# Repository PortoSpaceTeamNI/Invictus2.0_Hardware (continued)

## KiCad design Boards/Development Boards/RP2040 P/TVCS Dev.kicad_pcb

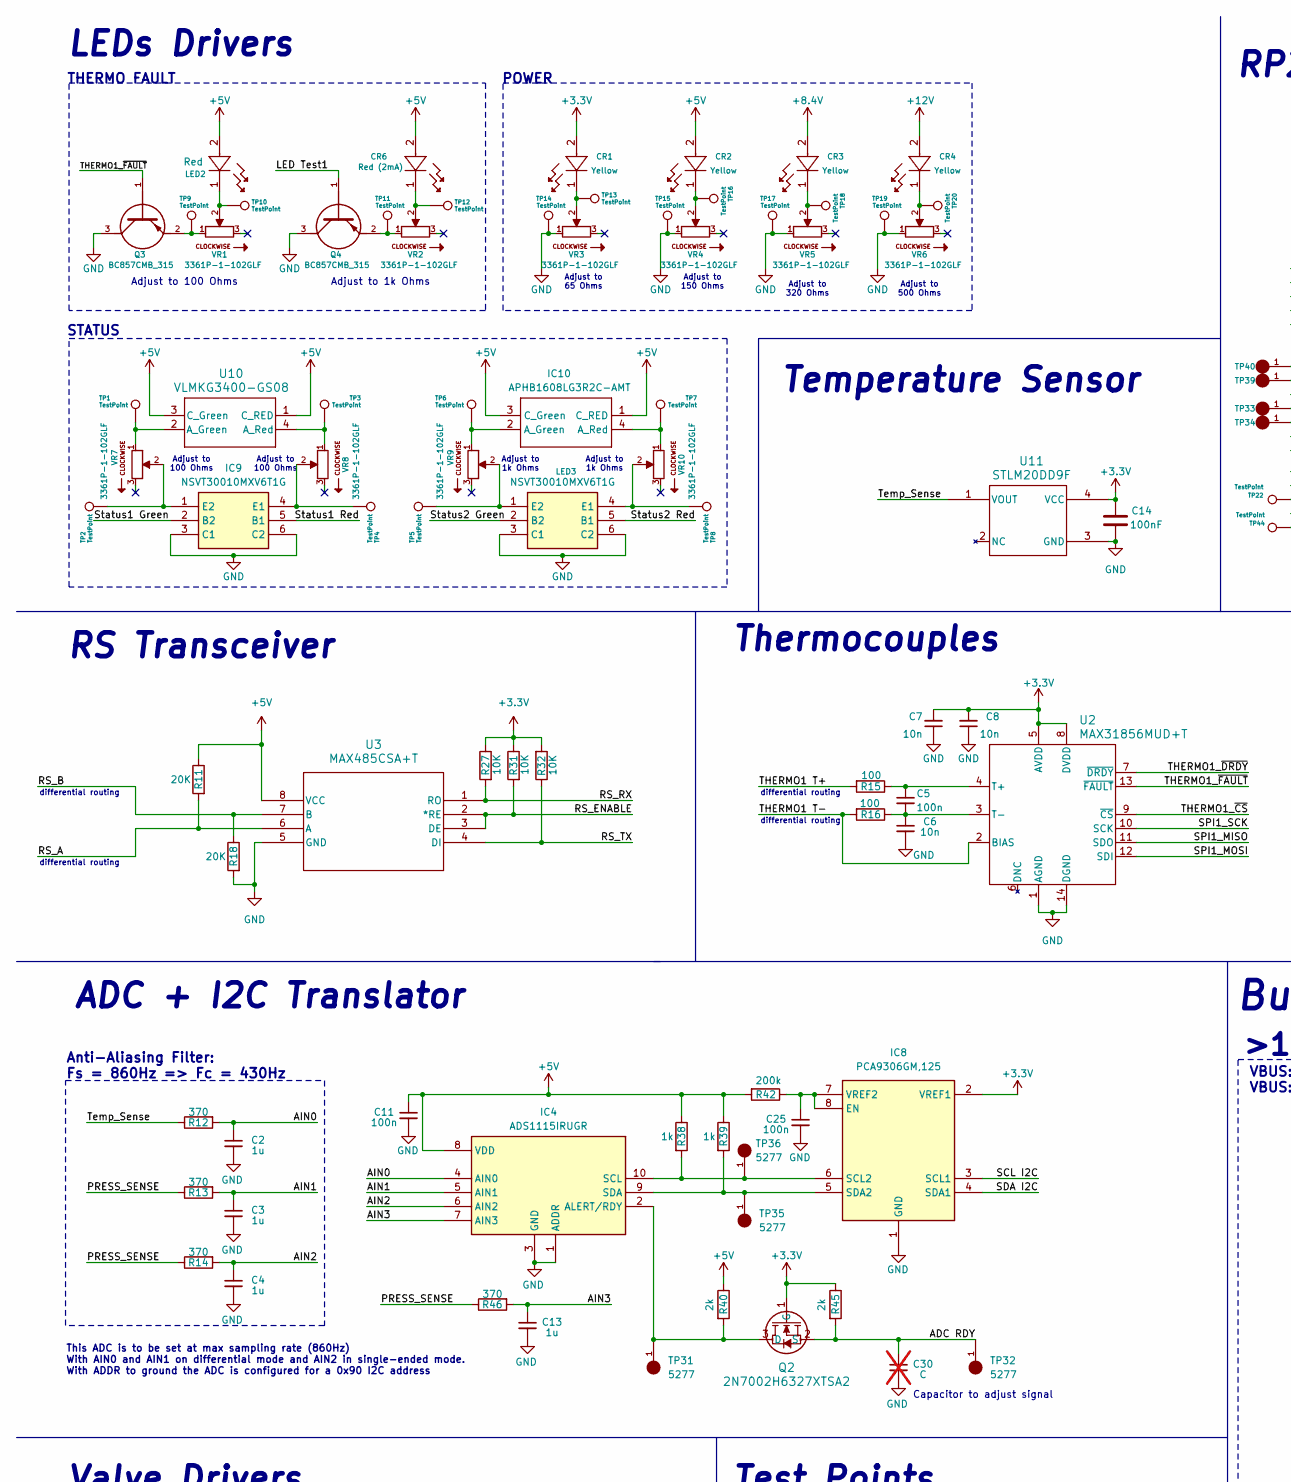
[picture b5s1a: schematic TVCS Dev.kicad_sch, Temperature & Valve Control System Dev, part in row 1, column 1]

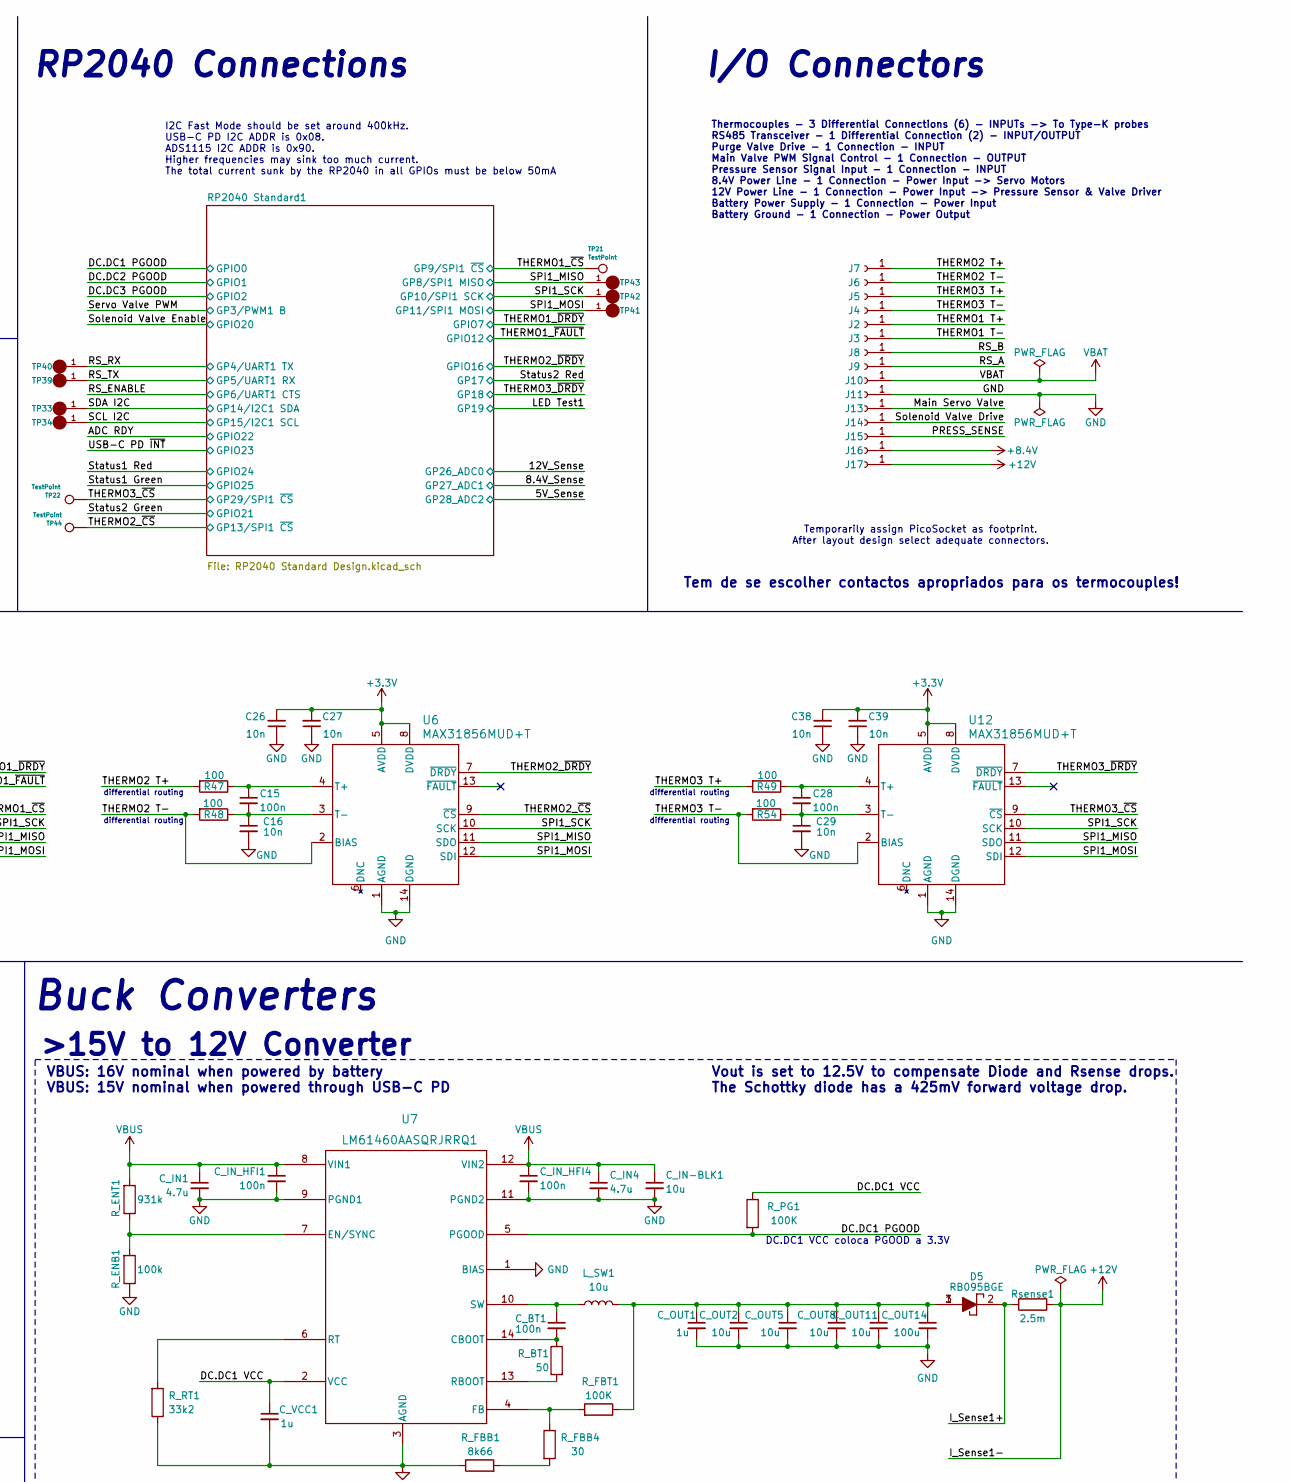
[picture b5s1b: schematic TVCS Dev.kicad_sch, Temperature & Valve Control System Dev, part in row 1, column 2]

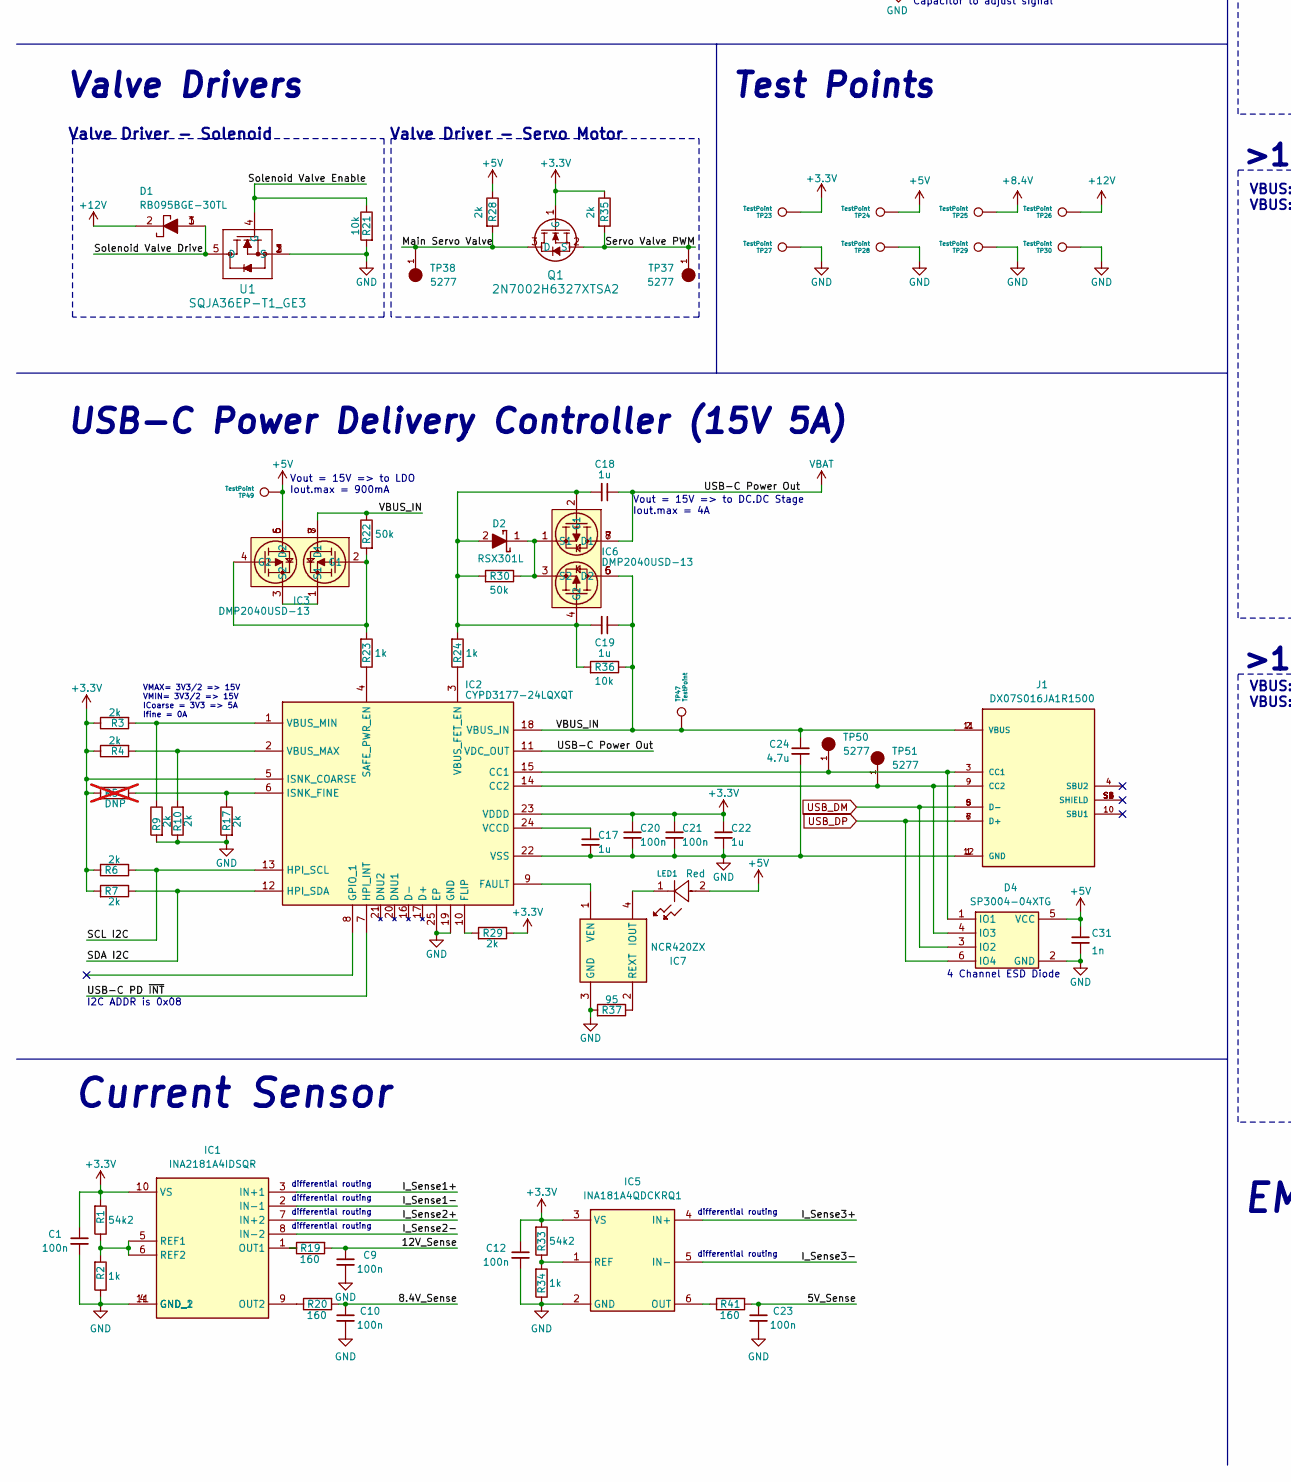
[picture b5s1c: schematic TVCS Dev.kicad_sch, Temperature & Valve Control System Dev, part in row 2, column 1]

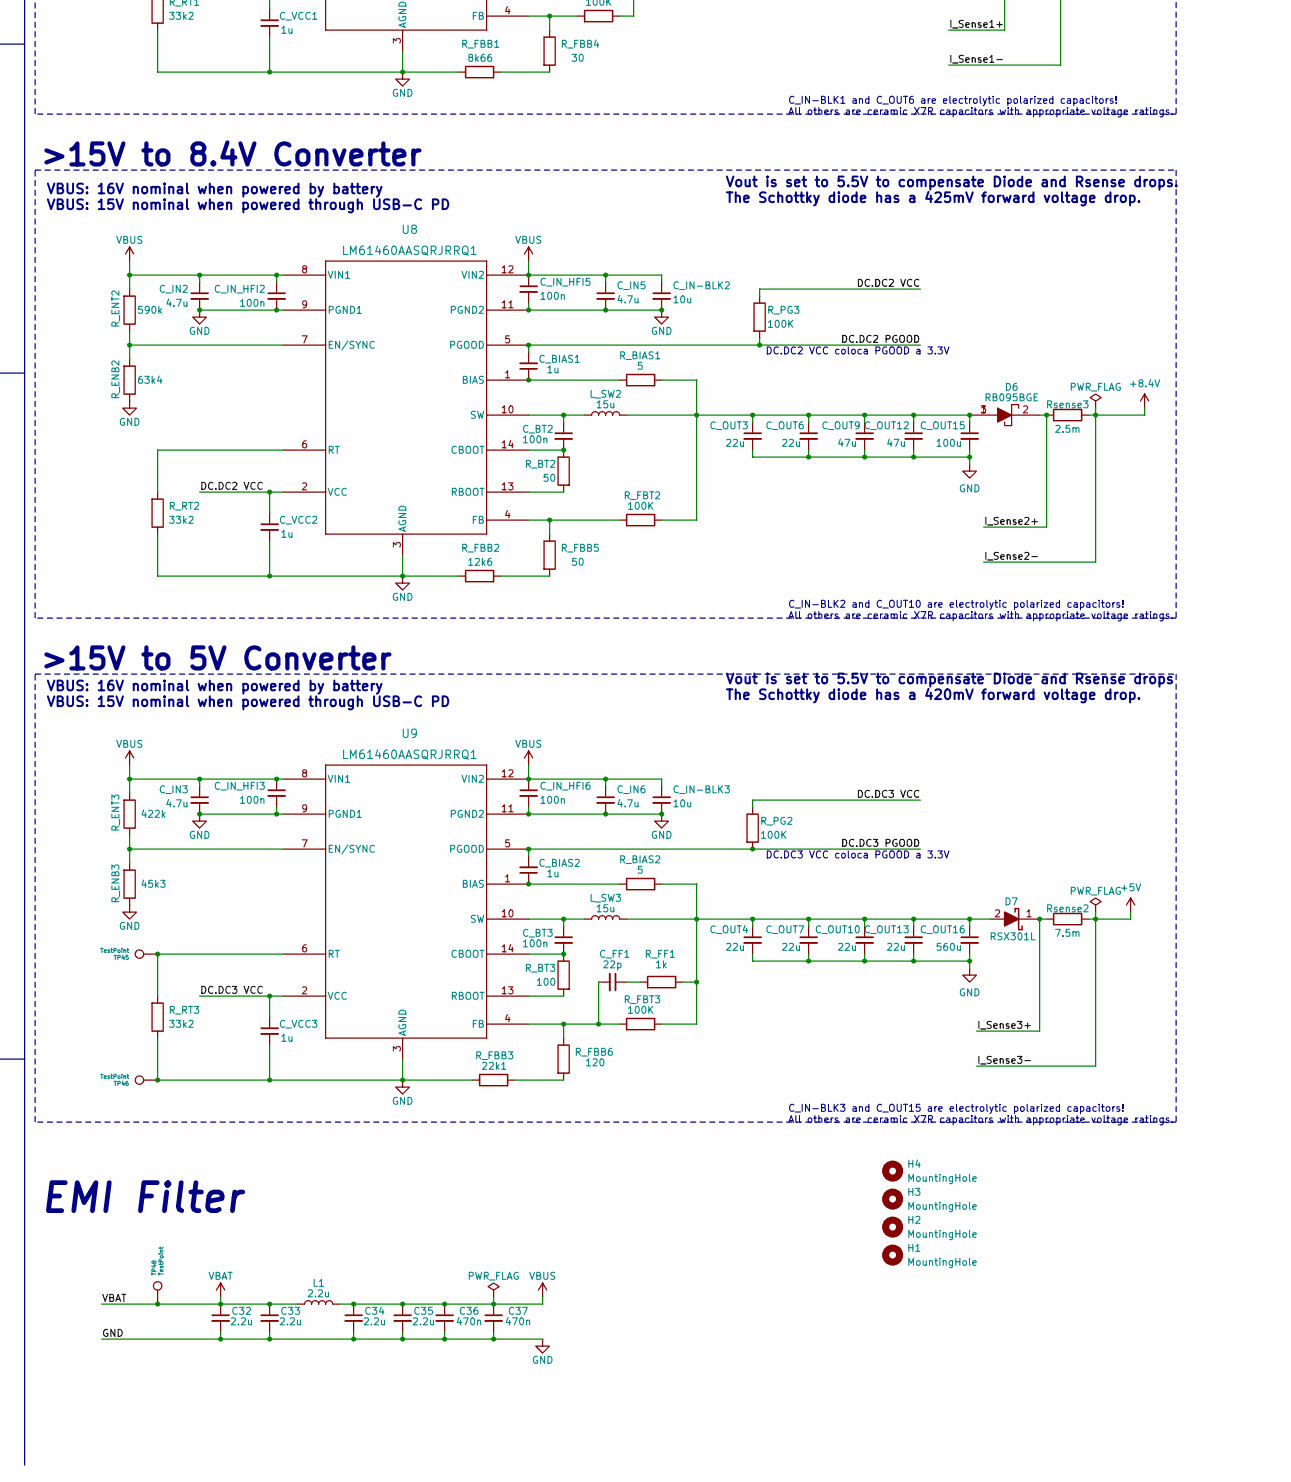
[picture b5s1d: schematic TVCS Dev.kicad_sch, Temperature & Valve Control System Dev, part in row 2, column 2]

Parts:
C1, C5, C9, C10, C11, C12, C15, C20, C21, C23, C25, C28: 100n; Capacitor_0402
C2, C3, C4, C13: 1u; Capacitor_0402
C6, C7, C8, C16, C26, C27, C29, C38, C39: 10n; Capacitor_0402
C14: 100nF; Capacitor_0402
C17, C18, C19, C22: 1u; Capacitor_0603
C24: 4.7u; Capacitor_1206
C30: C; Capacitor_0402; not fitted
C31: 1n; Capacitor_0402
C32, C33, C34, C35: 2.2u; Capacitor_0402
C36, C37: 470n; Capacitor_0402
CR1, CR2, CR3, CR4: VLMY1300-GS08; LEDC1608X100N
CR6: VLMT3100-GS08; LED_PLCC_VSMB
C_BIAS1, C_BIAS2: 1u; Capacitor_0603
C_BT1, C_BT2, C_BT3: 100n; Capacitor_0402
C_FF1: 22p; Capacitor_0402
C_IN1, C_IN2, C_IN3, C_IN4, C_IN5, C_IN6: 4.7u; Capacitor_1206
C_IN-BLK1, C_IN-BLK2, C_IN-BLK3: 10u; Capacitor_4mm
C_IN_HFI1, C_IN_HFI2, C_IN_HFI3, C_IN_HFI4, C_IN_HFI5, C_IN_HFI6: 100n; Capacitor_0402
C_OUT1: 1u; Capacitor_0603
C_OUT2, C_OUT5, C_OUT8, C_OUT11: 10u; Capacitor_0805
C_OUT3, C_OUT4, C_OUT6, C_OUT7, C_OUT10, C_OUT13: 22u; Capacitor_0805
C_OUT9, C_OUT12: 47u; Capacitor_0805
C_OUT14: 100u; Capacitor_6mm
C_OUT15: 100u; Capacitor_8mm
C_OUT16: 560u; Capacitor_8mm
C_VCC1, C_VCC2, C_VCC3: 1u; Capacitor_0603
D1: RB095BGE-30TL; RD3P175SNFRATL; Mouser Part Number 755-RB095BGE-30TL
D2, D7: RSX301L; DIOM5026X220N; Mouser Part Number 755-RSX301L-30DDTE25
D4: SP3004-04XTG; SOT563_LTF; Mouser Part Number 576-SP3004-04XTG
D5, D6: RB095BGE; RD3P175SNFRATL; Mouser Part Number 755-RB095BGE-30TL
H1, H2, H3, H4: MountingHole; MountingHole_3.2mm_M3_ISO7380_Pad_TopBottom
IC1: INA2181A4IDSQR; SON40P200X200X80-11N; Mouser Part Number 595-INA2181A4IDSQR
IC2: CYPD3177-24LQXQT; QFN50P400X400X60-25N-D; Mouser Part Number 727-CYPD3177-24LQXQT
IC3, IC6: DMP2040USD-13; SOIC127P600X175-8N; Mouser Part Number 621-DMP2040USD-13
IC4: ADS1115IRUGR; Mouser Part Number 595-ADS1115IRUGR
IC5: INA181A4QDCKRQ1; SOT65P210X110-6N; Mouser Part Number 595-INA181A4QDCKRQ1
IC7: NCR420ZX; SOT230P700X180-4N; Mouser Part Number 771-NCR420ZX
IC8: PCA9306GM,125; PCA9570GMH; Mouser Part Number 771-PCA9306GM125
IC9, IC10: NSVT30010MXV6T1G; SOT-563_1P3X1P7_ONS; Mouser Part Number 863-NSVT30010MXV6T1G
J1: DX07S016JA1R1500; JAE_DX07S016JA1R1500; PARTREV 1
J2, J3, J4, J5, J6, J7, J8, J9, J10, J11, J13, J14, J15, J16, J17: Conn_01x01_Socket; Pico_01pin
L1: 2.2u; Inductor_10.1x10
LED1, LED2: VLMS1500-GS08; LED_00-GS08_VIS_RED
LED3: APHB1608LG3R2C-AMT; APHB1608LG3R2CAMT; Mouser Part Number 604-APHB1608LG3R2CAM
L_SW1: 10u; Inductor_11.5x10
L_SW2, L_SW3: 15u; Inductor_10.1x10
Q1, Q2: 2N7002H6327XTSA2; PG-SOT23-3-5_INF_MIN
Q3, Q4: BC857CMB_315; TRANS_PMZB550UNEYL
R1, R33: 54k2; RES_0402
R2, R23, R24, R34, R38, R39: 1k; RES_0402
R3, R4, R6, R7, R9, R10, R17, R28, R29, R35, R40, R45: 2k; RES_0402
R5: DNP; RES_0402; not fitted
R11, R18: 20K; RES_0402
R12, R13, R14, R46: 370; RES_0402
R15, R16, R47, R48, R49, R54: 100; RES_0402
R19, R20, R41: 160; RES_0402
R21, R36: 10k; RES_0402
R22, R30: 50k; RES_0402
R27, R31, R32: 10K; RES_0402
R37: 95; RES_0402
R42: 200k; RES_0402
R_BIAS1, R_BIAS2: 5; RES_0402
R_BT1, R_BT2: 50; RES_0402
R_BT3: 100; RES_0402
R_ENB1: 100k; RES_0603
R_ENB2: 63k4; RES_0402
R_ENB3: 45k3; RES_0402
R_ENT1: 931k; RES_0603
R_ENT2: 590k; RES_0402
R_ENT3: 422k; RES_0402
R_FBB1: 8k66; RES_0603
R_FBB2: 12k6; RES_0603
R_FBB3: 22k1; RES_0603
R_FBB4: 30; RES_0603
R_FBB5: 50; RES_0603
R_FBB6: 120; RES_0603
R_FBT1, R_FBT2, R_FBT3: 100K; RES_0603
R_FF1: 1k; RES_0402
R_PG1, R_PG2, R_PG3: 100K; RES_0603
R_RT1, R_RT2, R_RT3: 33k2; RES_0603
Rsense1, Rsense3: 2.5m; RES_0805
Rsense2: 7.5m; RES_WSLP2512
TP1, TP2, TP3, TP4, TP5, TP6, TP7, TP8, TP9, TP10, TP11, TP12, TP13, TP14, TP15, TP16, TP17, TP18, TP19, TP20, TP21, TP22, TP23, TP24, TP25, TP26, TP27, TP28, TP29, TP30, TP44: TestPoint; TestPoint_Pad_2.0x2.0mm
TP31, TP32, TP33, TP34, TP35, TP36, TP37, TP38, TP39, TP40, TP41, TP42, TP43, TP50, TP51: 5277; KEYSTONE_5277
TP45, TP46, TP47, TP48, TP49: TestPoint; KEYSTONE_5277
U1: SQJA36EP-T1_GE3; PowerPAK_SO-8L_3_VIS
U2, U6, U12: MAX31856MUD+T; 21-0066J_14_MXM
U3: MAX485CSA+T; 21-0041-3-M_90-0096-8L_MXM
U7, U8, U9: LM61460AASQRJRRQ1; VQFN-HR14_RJR_TEX
U10: VLMKG3400-GS08; SMT_00-GS08_VIS
U11: STLM20DD9F; UDFN-4L_STM
VR1, VR2, VR3, VR4, VR5, VR6, VR7, VR8, VR9, VR10: 3361P-1-102GLF; TRIM_3361P-1-102GLF; PARTREV 08/19

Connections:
+3.3V: C1.1, C7.2, C8.2, C12.1, C14.1, C20.1, C21.1, C22.1, C26.2, C27.2, C38.2, C39.2, CR1.2, IC1.10 (VS), IC2.5 (ISNK_COARSE), IC2.23 (VDDD), IC5.3 (VS), IC8.2 (VREF1), Q1.1 (G), Q2.1 (G), R1.2, R3.1, R4.1, R5.2, R6.2, R7.2, R27.1, R29.1, R31.1, R32.2, R33.2, R35.1, R45.1, TP23.1, U2.5 (AVDD), U2.8 (DVDD), U6.5 (AVDD), U6.8 (DVDD), U11.4 (VCC), U12.5 (AVDD), U12.8 (DVDD); also elsewhere on the board
+5V: C11.1, C31.1, CR2.2, CR6.2, D4.5 (VCC), IC3.5 (D2), IC3.6 (D2), IC4.8 (VDD), IC5.5 (IN-), LED1.2, LED2.2, LED3.1 (C_RED), LED3.3 (C_Green), R11.1, R28.1, R38.1, R39.1, R40.1, R42.2, Rsense2.2, TP24.1, TP49.1, U3.8 (VCC), U10.1 (C_RED), U10.3 (C_Green); also elsewhere on the board
+8.4V: CR3.2, IC1.8 (IN-2), J16.1, Rsense3.2, TP25.1
+12V: CR4.2, D1.2, IC1.2 (IN-1), J17.1, Rsense1.2, TP26.1
/5V_Sense: C23.1, R41.2; also elsewhere on the board
/8.4V_Sense: C10.1, R20.2; also elsewhere on the board
/12V_Sense: C9.1, R19.2; also elsewhere on the board
/ADC RDY: C30.1, Q2.2 (S), R45.2, TP32.1; also elsewhere on the board
/AIN0: C2.1, IC4.4 (AIN0), R12.2
/AIN1: C3.1, IC4.5 (AIN1), R13.2
/AIN2: C4.1, IC4.6 (AIN2), R14.2
/AIN3: C13.1, IC4.7 (AIN3), R46.2
/DC.DC1 PGOOD: R_PG1.2, U7.5 (PGOOD); also elsewhere on the board
/DC.DC1 VCC: C_VCC1.1, R_PG1.1, U7.2 (VCC)
/DC.DC2 PGOOD: C_BIAS1.2, R_PG3.2, U8.5 (PGOOD); also elsewhere on the board
/DC.DC2 VCC: C_VCC2.1, R_PG3.1, U8.2 (VCC)
/DC.DC3 PGOOD: C_BIAS2.2, R_PG2.2, U9.5 (PGOOD); also elsewhere on the board
/DC.DC3 VCC: C_VCC3.1, R_PG2.1, U9.2 (VCC)
/I_Sense1+: D5.2, IC1.3 (IN+1), Rsense1.1
/I_Sense2+: D6.2, IC1.7 (IN+2), Rsense3.1
/I_Sense3+: D7.1 (K), IC5.4 (IN+), Rsense2.1
/LED Test1: Q4.1; also elsewhere on the board
/Main Servo Valve: J13.1, Q1.3 (D), R28.2, TP38.1
/PRESS_SENSE: J15.1, R13.1, R14.1, R46.1
/RS_A: J9.1, R11.2, U3.6 (A); also elsewhere on the board
/RS_B: J8.1, R18.1, U3.7 (B); also elsewhere on the board
/RS_ENABLE: R31.2, U3.2 (*RE), U3.3 (DE); also elsewhere on the board
/RS_RX: R27.2, TP40.1, U3.1 (RO); also elsewhere on the board
/RS_TX: R32.1, TP39.1, U3.4 (DI); also elsewhere on the board
/SCL I2C: IC2.13 (HPI_SCL), IC8.3 (SCL1), R6.1, TP34.1; also elsewhere on the board
/SDA I2C: IC2.12 (HPI_SDA), IC8.4 (SDA1), R7.1, TP33.1; also elsewhere on the board
/SPI1_MISO: TP43.1, U2.11 (SDO), U6.11 (SDO), U12.11 (SDO); also elsewhere on the board
/SPI1_MOSI: TP41.1, U2.12 (SDI), U6.12 (SDI), U12.12 (SDI); also elsewhere on the board
/SPI1_SCK: TP42.1, U2.10 (SCK), U6.10 (SCK), U12.10 (SCK); also elsewhere on the board
/Servo Valve PWM: Q1.2 (S), R35.2, TP37.1; also elsewhere on the board
/Solenoid Valve Drive: D1.1, D1.3, J14.1, U1.5 (D)
/Solenoid Valve Enable: R21.1, U1.4 (G); also elsewhere on the board
/Status1 Green: IC9.2 (B2); also elsewhere on the board
/Status1 Red: IC9.5 (B1); also elsewhere on the board
/Status2 Green: IC10.2 (B2); also elsewhere on the board
/Status2 Red: IC10.5 (B1); also elsewhere on the board
/THERMO1 T+: J2.1, R15.2
/THERMO1 T-: J3.1, R16.2, U2.2 (BIAS)
/THERMO1_~CS: TP21.1, U2.9 (~CS); also elsewhere on the board
/THERMO1_~DRDY: U2.7 (~DRDY); also elsewhere on the board
/THERMO1_~FAULT: Q3.1, U2.13 (~FAULT); also elsewhere on the board
/THERMO2 T+: J7.1, R47.2
/THERMO2 T-: J6.1, R48.2, U6.2 (BIAS)
/THERMO2_~CS: TP44.1, U6.9 (~CS); also elsewhere on the board
/THERMO2_~DRDY: U6.7 (~DRDY); also elsewhere on the board
/THERMO3 T+: J5.1, R49.2
/THERMO3 T-: J4.1, R54.2, U12.2 (BIAS)
/THERMO3_~CS: TP22.1, U12.9 (~CS); also elsewhere on the board
/THERMO3_~DRDY: U12.7 (~DRDY); also elsewhere on the board
/Temp_Sense: R12.1, U11.1 (VOUT)
/USB-C PD ~INT: IC2.7 (HPI_INT); also elsewhere on the board
/VBUS_IN: C19.1, C24.1, IC2.18 (VBUS_IN), IC3.7 (D1), IC3.8 (D1), IC6.5 (D2), IC6.6 (D2), J1.2 (VBUS), J1.11 (VBUS), R22.1, R36.1, TP47.1
GND: C1.2, C2.2, C3.2, C4.2, C6.2, C7.1, C8.1, C9.2, C10.2, C11.2, C12.2, C13.2, C14.2, C16.2, C17.2, C20.2, C21.2, C22.2, C23.2, C24.2, C25.2, C26.1, C27.1, C29.2, C30.2, C31.2, C32.2, C33.2, C34.2, C35.2, C36.2, C37.2, C38.1, C39.1, C_IN1.2, C_IN2.2, C_IN3.2, C_IN4.2, C_IN5.2, C_IN6.2, C_IN-BLK1.2, C_IN-BLK2.2, C_IN-BLK3.2, C_IN_HFI1.2, C_IN_HFI2.2, C_IN_HFI3.2, C_IN_HFI4.2, C_IN_HFI5.2, C_IN_HFI6.2, C_OUT1.2, C_OUT2.2, C_OUT3.2, C_OUT4.2, C_OUT5.2, C_OUT6.2, C_OUT7.2, C_OUT8.2, C_OUT9.2, C_OUT10.2, C_OUT11.2, C_OUT12.2, C_OUT13.2, C_OUT14.2, C_OUT15.2, C_OUT16.2, C_VCC1.2, C_VCC2.2, C_VCC3.2, D4.2 (GND), IC1.4 (GND_1), IC1.11 (GND_2), IC2.19 (GND), IC2.22 (VSS), IC2.25 (EP), IC4.1 (ADDR), IC4.3 (GND), IC5.2 (GND), IC7.3 (GND), IC8.1 (GND), IC9.3 (C1), IC9.6 (C2), IC10.3 (C1), IC10.6 (C2), J1.1 (GND), J1.12 (GND), J11.1, Q3.3, Q4.3, R2.1, R9.2, R10.1, R17.2, R18.2, R21.2, R34.1, R37.2, R_ENB1.1, R_ENB2.1, R_ENB3.1, R_FBB1.1, R_FBB2.1, R_FBB3.1, R_RT1.1, R_RT2.1, R_RT3.1, TP14.1, TP15.1, TP17.1, TP19.1, TP27.1, TP28.1, TP29.1, TP30.1, TP46.1, U1.1 (S), U1.2 (S), U1.3 (S), U2.1 (AGND), U2.14 (DGND), U3.5 (GND), U6.1 (AGND), U6.14 (DGND), U7.1 (BIAS), U7.3 (AGND), U7.9 (PGND1), U7.11 (PGND2), U8.3 (AGND), U8.9 (PGND1), U8.11 (PGND2), U9.3 (AGND), U9.9 (PGND1), U9.11 (PGND2), U11.3 (GND), U12.1 (AGND), U12.14 (DGND), VR3.1, VR4.1, VR5.1, VR6.1; also elsewhere on the board
unnamed: CR1.1, TP13.1, VR3.2
unnamed: CR2.1, TP16.1, VR4.2
unnamed: CR3.1, TP18.1, VR5.2
unnamed: CR4.1, TP20.1, VR6.2
unnamed: CR6.1, TP12.1, VR2.2
unnamed: C_FF1.1, R_FF1.2
unnamed: C_OUT1.1, C_OUT2.1, C_OUT5.1, C_OUT8.1, C_OUT11.1, C_OUT14.1, D5.1, D5.3, L_SW1.2, R_FBT1.1
unnamed: C_OUT3.1, C_OUT6.1, C_OUT9.1, C_OUT12.1, C_OUT15.1, D6.1, D6.3, L_SW2.2, R_BIAS1.2, R_FBT2.1
unnamed: C18.2, C19.2, D2.2 (A), IC6.2 (G1), IC6.4 (G2), R24.2, R30.2, R36.2
unnamed: D2.1 (K), IC6.1 (S1), IC6.3 (S2), R30.1
unnamed: D4.1 (IO1), IC2.15 (CC1), J1.3 (CC1), TP50.1
unnamed: D4.4 (IO3), IC2.14 (CC2), J1.9 (CC2), TP51.1
unnamed: C_OUT4.1, C_OUT7.1, C_OUT10.1, C_OUT13.1, C_OUT16.1, D7.2 (A), L_SW3.2, R_BIAS2.2, R_FBT3.1, R_FF1.1
unnamed: IC1.1 (OUT1), R19.1
unnamed: IC1.9 (OUT2), R20.1
unnamed: IC1.5 (REF1), IC1.6 (REF2), R1.1, R2.2
unnamed: IC2.9 (FAULT), IC7.1 (VEN)
unnamed: IC2.10 (FLIP), R29.2
unnamed: IC2.6 (ISNK_FINE), R5.1, R17.1
unnamed: IC2.4 (SAFE_PWR_EN), R23.1
unnamed: IC2.3 (VBUS_FET_EN), R24.1
unnamed: IC2.2 (VBUS_MAX), R4.2, R10.2
unnamed: IC2.1 (VBUS_MIN), R3.2, R9.1
unnamed: C17.1, IC2.24 (VCCD)
unnamed: IC3.2 (G1), IC3.4 (G2), R22.2, R23.2
unnamed: IC3.1 (S1), IC3.3 (S2)
unnamed: IC4.2 (ALERT/RDY), Q2.3 (D), R40.2, TP31.1
unnamed: IC4.10 (SCL), IC8.6 (SCL2), R38.2, TP36.1
unnamed: IC4.9 (SDA), IC8.5 (SDA2), R39.2, TP35.1
unnamed: IC5.6 (OUT), R41.1
unnamed: IC5.1 (REF), R33.1, R34.2
unnamed: IC7.4 (IOUT), LED1.1
unnamed: IC7.2 (REXT), R37.1
unnamed: C25.1, IC8.7 (VREF2), IC8.8 (EN), R42.1
unnamed: IC9.4 (E1), TP4.1, VR8.2
unnamed: IC9.1 (E2), TP2.1, VR7.2
unnamed: IC10.4 (E1), TP8.1, VR10.2
unnamed: IC10.1 (E2), TP5.1, VR9.2
unnamed: LED2.1, TP10.1, VR1.2
unnamed: LED3.2 (A_Green), TP6.1, VR9.1
unnamed: LED3.4 (A_Red), TP7.1, VR10.1
unnamed: Q3.2, TP9.1, VR1.1
unnamed: Q4.2, TP11.1, VR2.1
unnamed: R_FBB1.2, R_FBB4.2
unnamed: R_FBB2.2, R_FBB5.2
unnamed: R_FBB3.2, R_FBB6.2
unnamed: C5.1, R15.1, U2.4 (T+)
unnamed: C5.2, C6.1, R16.1, U2.3 (T-)
unnamed: C15.1, R47.1, U6.4 (T+)
unnamed: C15.2, C16.1, R48.1, U6.3 (T-)
unnamed: C_BT1.2, R_BT1.1, U7.14 (CBOOT)
unnamed: R_ENB1.2, R_ENT1.1, U7.7 (EN/SYNC)
unnamed: R_FBB4.1, R_FBT1.2, U7.4 (FB)
unnamed: R_BT1.2, U7.13 (RBOOT)
unnamed: R_RT1.2, U7.6 (RT)
unnamed: C_BT1.1, L_SW1.1, U7.10 (SW)
unnamed: C_BIAS1.1, R_BIAS1.1, U8.1 (BIAS)
unnamed: C_BT2.2, R_BT2.1, U8.14 (CBOOT)
unnamed: R_ENB2.2, R_ENT2.1, U8.7 (EN/SYNC)
unnamed: R_FBB5.1, R_FBT2.2, U8.4 (FB)
unnamed: R_BT2.2, U8.13 (RBOOT)
unnamed: R_RT2.2, U8.6 (RT)
unnamed: C_BT2.1, L_SW2.1, U8.10 (SW)
unnamed: C_BIAS2.1, R_BIAS2.1, U9.1 (BIAS)
unnamed: C_BT3.2, R_BT3.1, U9.14 (CBOOT)
unnamed: R_ENB3.2, R_ENT3.1, U9.7 (EN/SYNC)
unnamed: C_FF1.2, R_FBB6.1, R_FBT3.2, U9.4 (FB)
unnamed: R_BT3.2, U9.13 (RBOOT)
unnamed: R_RT3.2, TP45.1, U9.6 (RT)
unnamed: C_BT3.1, L_SW3.1, U9.10 (SW)
unnamed: TP1.1, U10.2 (A_Green), VR7.1
unnamed: TP3.1, U10.4 (A_Red), VR8.1
unnamed: C28.1, R49.1, U12.4 (T+)
unnamed: C28.2, C29.1, R54.1, U12.3 (T-)
USB_DM: D4.3 (IO2), J1.5 (D-), J1.8 (D-); also elsewhere on the board
USB_DP: D4.6 (IO4), J1.6 (D+), J1.7 (D+); also elsewhere on the board
VBAT: C18.1, C32.1, C33.1, IC2.11 (VDC_OUT), IC6.7 (D1), IC6.8 (D1), J10.1, L1.1, TP48.1
VBUS: C34.1, C35.1, C36.1, C37.1, C_IN1.1, C_IN2.1, C_IN3.1, C_IN4.1, C_IN5.1, C_IN6.1, C_IN-BLK1.1, C_IN-BLK2.1, C_IN-BLK3.1, C_IN_HFI1.1, C_IN_HFI2.1, C_IN_HFI3.1, C_IN_HFI4.1, C_IN_HFI5.1, C_IN_HFI6.1, L1.2, R_ENT1.2, R_ENT2.2, R_ENT3.2, U7.8 (VIN1), U7.12 (VIN2), U8.8 (VIN1), U8.12 (VIN2), U9.8 (VIN1), U9.12 (VIN2)

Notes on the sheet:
Vout is set to 5.5V to compensate Diode and Rsense drops. The Schottky diode has a 425mV forward voltage drop.
Temporarily assign PicoSocket as footprint. After layout design select adequate connectors.
differential routing
Anti-Aliasing Filter: Fs = 860Hz => Fc = 430Hz
LEDs Drivers
>15V to 5V Converter
I2C Fast Mode should be set around 400kHz. USB-C PD I2C ADDR is 0x08. ADS1115 I2C ADDR is 0x90. Higher frequencies may sink too much current. The total current sunk by the RP2040 in all GPIOs must be below 50mA
DC.DC2 VCC coloca PGOOD a 3.3V
POWER
Thermocouples - 3 Differential Connections (6) - INPUTs -> To Type-K probes RS485 Transceiver - 1 Differential Connection (2) - INPUT/OUTPUT Purge Valve Drive - 1 Connection - INPUT Main Valve PWM Signal Control - 1 Connection - OUTPUT Pressure Sensor Signal Input - 1 Connection - INPUT 8.4V Power 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
I2C ADDR is 0x08
This ADC is to be set at max sampling rate (860Hz) With AIN0 and AIN1 on differential mode and AIN2 in single-ended mode. With ADDR to ground the ADC is configured for a 0x90 I2C address
Adjust to 150 Ohms
STATUS
Vout is set to 5.5V to compensate Diode and Rsense drops The Schottky diode has a 420mV forward voltage drop.
Adjust to 1k Ohms
Valve Driver - Solenoid
Valve Driver - Servo Motor
Adjust to 500 Ohms
Adjust to 100 Ohms
Adjust to 65 Ohms
DC.DC1 VCC coloca PGOOD a 3.3V
Valve Drivers
VBUS: 16V nominal when powered by battery VBUS: 15V nominal when powered through USB-C PD
Vout = 15V => to LDO Iout.max = 900mA
Current Sensor
RS Transceiver
>15V to 12V Converter
C_IN-BLK3 and C_OUT15 are electrolytic polarized capacitors! All others are ceramic X7R capacitors with appropriate voltage ratings.
VMAX= 3V3/2 => 15V VMIN= 3V3/2 => 15V ICoarse = 3V3 => 5A Ifine = 0A
DC.DC3 VCC coloca PGOOD a 3.3V
EMI Filter
ADC + I2C Translator
USB-C Power Delivery Controller (15V 5A)
Tem de se escolher contactos apropriados para os termocouples!
Capacitor to adjust signal
C_IN-BLK1 and C_OUT6 are electrolytic polarized capacitors! All others are ceramic X7R capacitors with appropriate voltage ratings.
4 Channel ESD Diode
Vout = 15V => to DC.DC Stage Iout.max = 4A
Vout is set to 12.5V to compensate Diode and Rsense drops. The Schottky diode has a 425mV forward voltage drop.

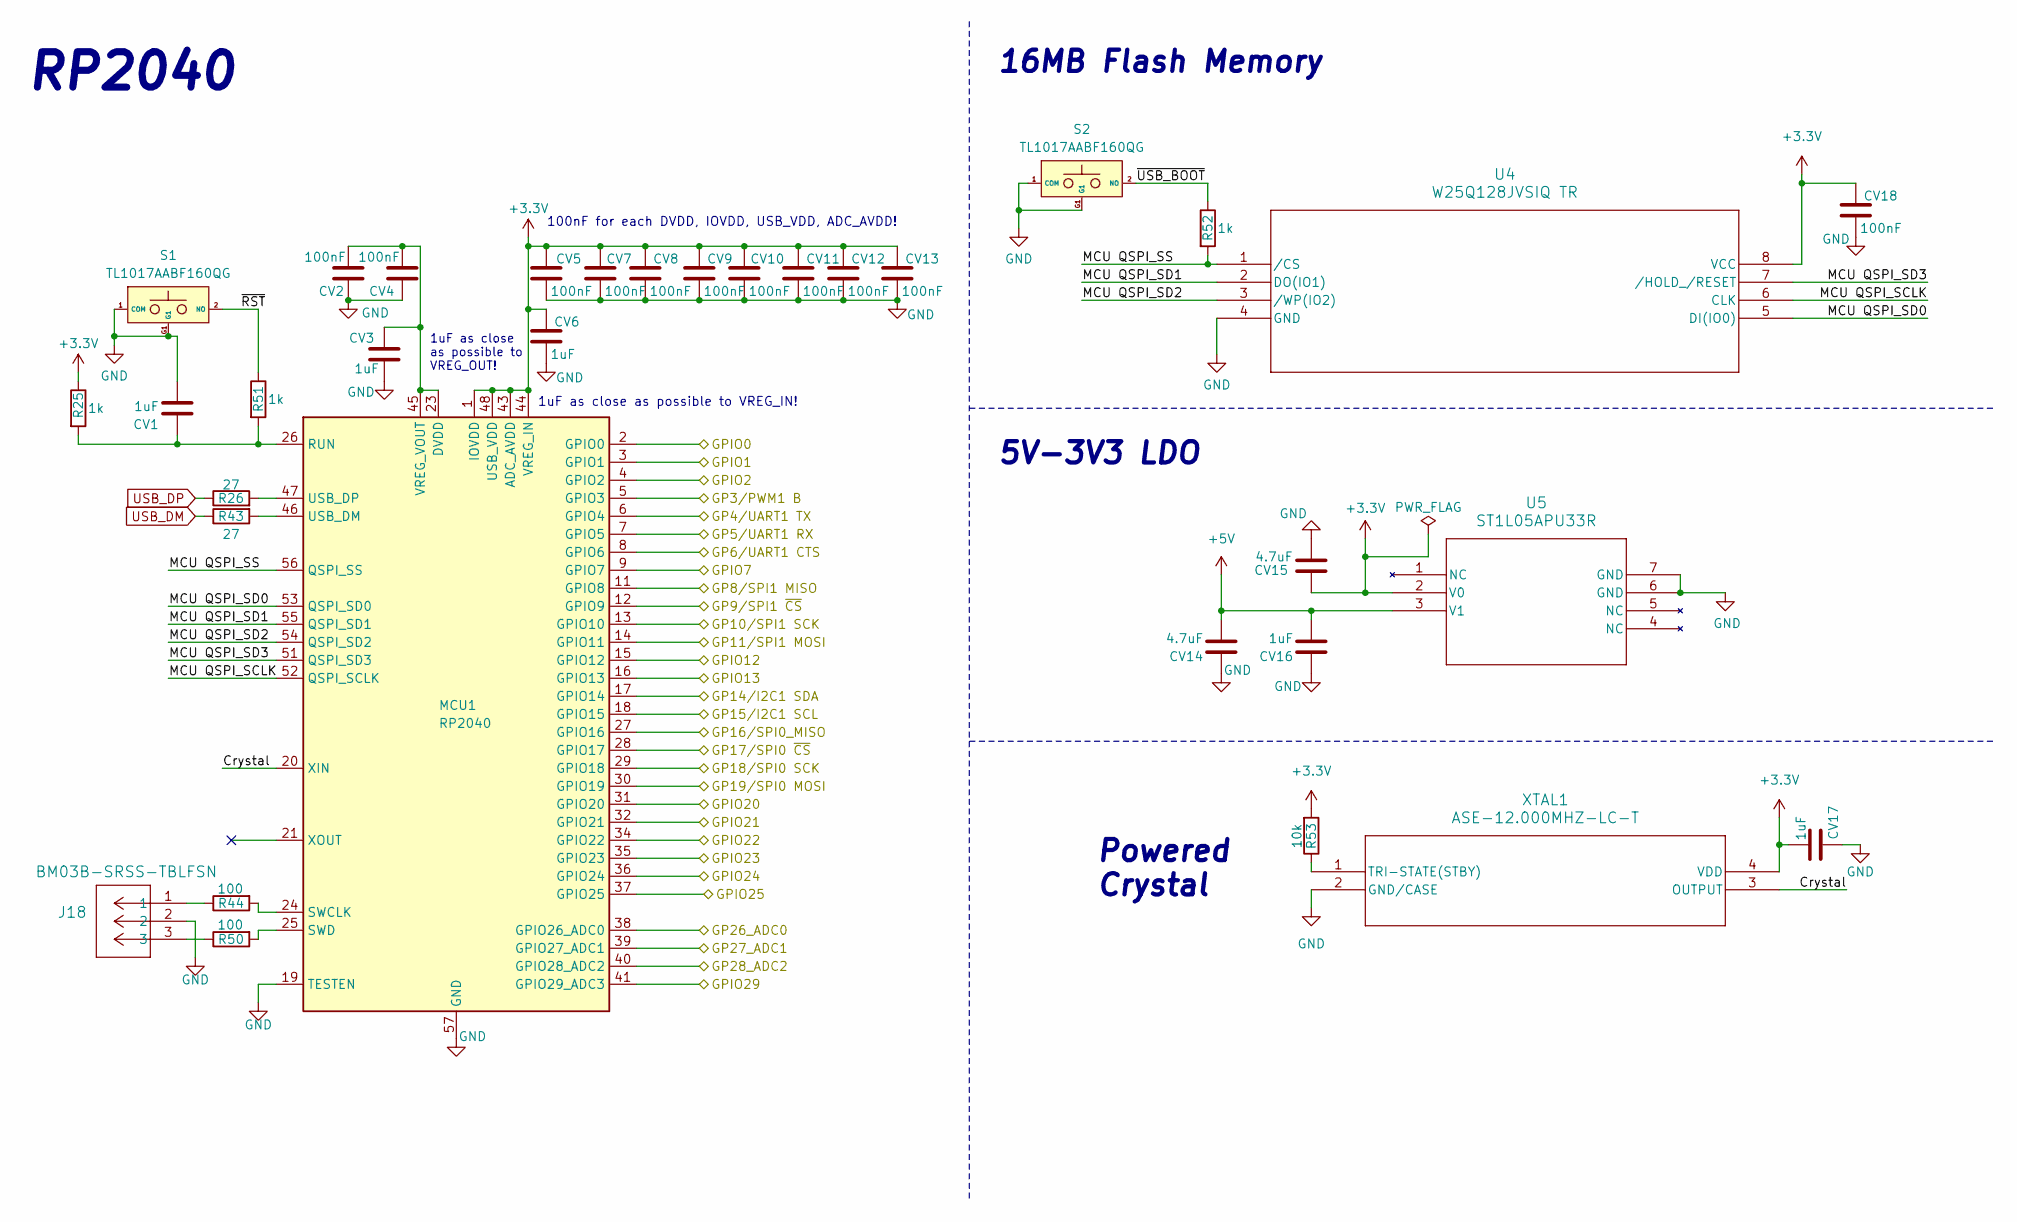
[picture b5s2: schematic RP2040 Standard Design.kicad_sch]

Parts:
CV1, CV3, CV6, CV16, CV17: 1uF; Capacitor_0402
CV2, CV4, CV5, CV7, CV8, CV9, CV10, CV11, CV12, CV13, CV18: 100nF; Capacitor_0402
CV14, CV15: 4.7uF; Capacitor_0402
J18: BM03B-SRSS-TBLFSN; CONN_BM03B-SRSS-TBLFSN_JST
MCU1: RP2040; QFN-56-1EP_7x7mm_P0.4mm_EP3.2x3.2mm
R25, R51, R52: 1k; RES_0402
R26, R43: 27; RES_0603
R44, R50: 100; RES_0402
R53: 10k; RES_0402
S1, S2: TL1017AABF160QG; Mouser Part Number 612-TL1017AABF160QG
U4: W25Q128JVSIQ TR; SOIC_208MIL_WIN
U5: ST1L05APU33R; DFN_5APU33R_STM
XTAL1: ASE-12.000MHZ-LC-T; ASE24576MHZLCT

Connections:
+3.3V: CV5.1, CV6.1, CV7.1, CV8.1, CV9.1, CV10.1, CV11.1, CV12.1, CV13.1, CV15.2, CV17.1, CV18.1, MCU1.1 (IOVDD), MCU1.10 (IOVDD), MCU1.22 (IOVDD), MCU1.33 (IOVDD), MCU1.42 (IOVDD), MCU1.43 (ADC_AVDD), MCU1.44 (VREG_IN), MCU1.48 (USB_VDD), MCU1.49 (IOVDD), R25.1, R53.2, U4.8 (VCC), U5.2 (V0), XTAL1.4 (VDD); also elsewhere on the board
+5V: CV14.2, CV16.2, U5.3 (V1); also elsewhere on the board
/5V_Sense: MCU1.40 (GPIO28_ADC2); also elsewhere on the board
/8.4V_Sense: MCU1.39 (GPIO27_ADC1); also elsewhere on the board
/12V_Sense: MCU1.38 (GPIO26_ADC0); also elsewhere on the board
/ADC RDY: MCU1.34 (GPIO22); also elsewhere on the board
/DC.DC1 PGOOD: MCU1.2 (GPIO0); also elsewhere on the board
/DC.DC2 PGOOD: MCU1.3 (GPIO1); also elsewhere on the board
/DC.DC3 PGOOD: MCU1.4 (GPIO2); also elsewhere on the board
/LED Test1: MCU1.30 (GPIO19); also elsewhere on the board
/RP2040 Standard1/Crystal: MCU1.20 (XIN), XTAL1.3 (OUTPUT)
/RP2040 Standard1/MCU QSPI_SCLK: MCU1.52 (QSPI_SCLK), U4.6 (CLK)
/RP2040 Standard1/MCU QSPI_SD0: MCU1.53 (QSPI_SD0), U4.5 (DI(IO0))
/RP2040 Standard1/MCU QSPI_SD1: MCU1.55 (QSPI_SD1), U4.2 (DO(IO1))
/RP2040 Standard1/MCU QSPI_SD2: MCU1.54 (QSPI_SD2), U4.3 (/WP(IO2))
/RP2040 Standard1/MCU QSPI_SD3: MCU1.51 (QSPI_SD3), U4.7 (/HOLD_/RESET)
/RP2040 Standard1/MCU QSPI_SS: MCU1.56 (QSPI_SS), R52.2, U4.1 (/CS)
/RP2040 Standard1/~RST: R51.1, S1.2 (NO); also elsewhere on the board
/RP2040 Standard1/~USB_BOOT: R52.1, S2.2 (NO); also elsewhere on the board
/RS_ENABLE: MCU1.8 (GPIO6); also elsewhere on the board
/RS_RX: MCU1.6 (GPIO4); also elsewhere on the board
/RS_TX: MCU1.7 (GPIO5); also elsewhere on the board
/SCL I2C: MCU1.18 (GPIO15); also elsewhere on the board
/SDA I2C: MCU1.17 (GPIO14); also elsewhere on the board
/SPI1_MISO: MCU1.11 (GPIO8); also elsewhere on the board
/SPI1_MOSI: MCU1.14 (GPIO11); also elsewhere on the board
/SPI1_SCK: MCU1.13 (GPIO10); also elsewhere on the board
/Servo Valve PWM: MCU1.5 (GPIO3); also elsewhere on the board
/Solenoid Valve Enable: MCU1.31 (GPIO20); also elsewhere on the board
/Status1 Green: MCU1.37 (GPIO25); also elsewhere on the board
/Status1 Red: MCU1.36 (GPIO24); also elsewhere on the board
/Status2 Green: MCU1.32 (GPIO21); also elsewhere on the board
/Status2 Red: MCU1.28 (GPIO17); also elsewhere on the board
/THERMO1_~CS: MCU1.12 (GPIO9); also elsewhere on the board
/THERMO1_~DRDY: MCU1.9 (GPIO7); also elsewhere on the board
/THERMO1_~FAULT: MCU1.15 (GPIO12); also elsewhere on the board
/THERMO2_~CS: MCU1.16 (GPIO13); also elsewhere on the board
/THERMO2_~DRDY: MCU1.27 (GPIO16); also elsewhere on the board
/THERMO3_~CS: MCU1.41 (GPIO29_ADC3); also elsewhere on the board
/THERMO3_~DRDY: MCU1.29 (GPIO18); also elsewhere on the board
/USB-C PD ~INT: MCU1.35 (GPIO23); also elsewhere on the board
GND: CV1.2, CV2.1, CV3.2, CV4.1, CV5.2, CV6.2, CV7.2, CV8.2, CV9.2, CV10.2, CV11.2, CV12.2, CV13.2, CV14.1, CV15.1, CV16.1, CV17.2, CV18.2, J18.2, MCU1.19 (TESTEN), MCU1.57 (GND), S1.1 (COM), S1.G1, S2.1 (COM), S2.G1, U4.4 (GND), U5.6 (GND), U5.7 (GND), XTAL1.2 (GND/CASE); also elsewhere on the board
unnamed: J18.1, R44.1
unnamed: J18.3, R50.1
unnamed: CV1.1, MCU1.26 (RUN), R25.2, R51.2
unnamed: MCU1.24 (SWCLK), R44.2
unnamed: MCU1.25 (SWD), R50.2
unnamed: MCU1.46 (USB_DM), R43.2
unnamed: MCU1.47 (USB_DP), R26.2
unnamed: CV2.2, CV3.1, CV4.2, MCU1.23 (DVDD), MCU1.45 (VREG_VOUT), MCU1.50 (DVDD)
unnamed: R53.1, XTAL1.1 (TRI-STATE(STBY))
USB_DM: R43.1; also elsewhere on the board
USB_DP: R26.1; also elsewhere on the board

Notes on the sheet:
1uF as close as possible to VREG_OUT!
Powered Crystal
16MB Flash Memory
100nF for each DVDD, IOVDD, USB_VDD, ADC_AVDD!
5V-3V3 LDO
1uF as close as possible to VREG_IN!
RP2040
